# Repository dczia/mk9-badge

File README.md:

```
___  ____     _____  ______           _            
|  \/  | |   |  _  | | ___ \         | |           
| .  . | | __| |_| | | |_/ / __ _  __| | __ _  ___ 
| |\/| | |/ /\____ | | ___ \/ _` |/ _` |/ _` |/ _ \
| |  | |   < .___/ / | |_/ / (_| | (_| | (_| |  __/
\_|  |_/_|\_\\____/  \____/ \__,_|\__,_|\__, |\___|
                                         __/ |     
                                        |___/      
-------------------------------------------------
D C Z I A  ----------  2 0 2 6
```

DCZia Presents: The MK9 Badge

It blinks. It types. You can wear it around your neck and then set it on your desk and actually use it\*.

\* _Desk productivity not guaranteed. DCZia assumes no responsibility for keys accidentally sent during badge parties. Consult your keyboard layer documentation before operating heavy machinery._

---

## About

The **MK9** is a fully functional **3×3 mechanical macropad badge**. Nine real mechanical switches, per-key RGB lighting, ambient underglow, an accelerometer that actually does something interesting, SAO support, and CircuitPython firmware out of the box — all in a package sized to hang around your neck at DEF CON and survive the week.

---

## Specs

**Keys**
- 9× mechanical switches in a 3×3 grid — standard MX footprint, swap keycaps as you please
- Ships with translucent blue keycaps
- Full N-key rollover USB HID keyboard when plugged into a computer

**Lighting**
- 9× WS2812B per-key RGB LEDs — one under each switch
- 6× SK6812 side-firing LEDs — edge-mounted for ambient underglow out the sides

**Brains & Sensors**
- RP2040 microcontroller
- 3-axis accelerometer — tilt-reactive lighting, shake to change patterns
- 2× SAO connectors (standard 6-pin, I2C + 2 GPIO each) — expand with the badge add-on ecosystem

**Power & I/O**
- USB-C — power and data
- 3× AAA battery pack — run it untethered
- Power switch for battery mode
- Reset button + BOOTSEL button for easy firmware flashing

**Firmware**
- Ships with CircuitPython firmware
- QMK-compatible hardware — reflash and run it as a full QMK macropad

---

## What It Does Out of the Box

On boot: a rainbow diagonal wipe sweeps across the keys and backlights. Any keypress skips it.

Once running:
- Background light patterns cycle across all 15 LEDs — rainbow wave, breathing pulse, or sparkle
- Pressing a key sends a colour ripple expanding outward from that key through all the LEDs
- Tilt the badge to shift the colour palette; shake it to switch patterns
- Plug into a computer and it shows up as a numpad (7–9 / 4–6 / 1–3 layout)

---

## Repository

```
mk9-badge/
├── buildguide.md — badge assembly, flashing, and troubleshooting
├── hardware/   — KiCad design files, BOM, fabrication outputs
└── software/   — MicroPython firmware
```

- [Build Guide →](buildguide.md) — assembly, battery installation, flashing, and troubleshooting
- [Hardware →](hardware/README.md) — schematics, PCB layout, drill files, BOM
- [Software →](software/README.md) — firmware architecture, pinout, library requirements, flashing instructions

**Fabrication outputs**:
- [PCB layer plot](hardware/output/mk9-badge.pdf)
- [PTH drill map](hardware/output/mk9-badge-PTH-drl_map.pdf)
- [NPTH drill map](hardware/output/mk9-badge-NPTH-drl_map.pdf)

---

## Programming / Updating

The badge runs [CircuitPython](https://circuitpython.org). To update the firmware:

1. Hold **BOOTSEL** while plugging the badge into your computer — it mounts as `RPI-RP2`.
2. Drag the CircuitPython `.uf2` onto the drive. It reboots as `CIRCUITPY`.
3. Copy the `lib/` folder contents to `CIRCUITPY/lib/` (see [software/README.md](software/README.md) for the library list).
4. Copy all `.py` files from `software/` to the root of `CIRCUITPY`.

The badge restarts automatically. If it gets into a weird state, delete everything on `CIRCUITPY` and start fresh — it won't brick.

Want to run QMK instead? The hardware is fully compatible; QMK setup instructions will be posted separately.

**Recommended IDEs:** Visual Studio Code with the [CircuitPython extension](https://marketplace.visualstudio.com/items?itemName=ms-python.python), or [Thonny](https://thonny.org). A Commodore 64 with a serial adapter also works but is left as an exercise for the reader.

---

## Open Source

DCZia is committed to open source hardware and software. All design files and firmware are publicly available.

- **Live CAD (OnShape):** [View the design](https://cad.onshape.com/documents/36884624fbe35c16a5af61a7/w/233227193d278274727a44c3/e/ea987b4b53c4648fa3dc84b6)

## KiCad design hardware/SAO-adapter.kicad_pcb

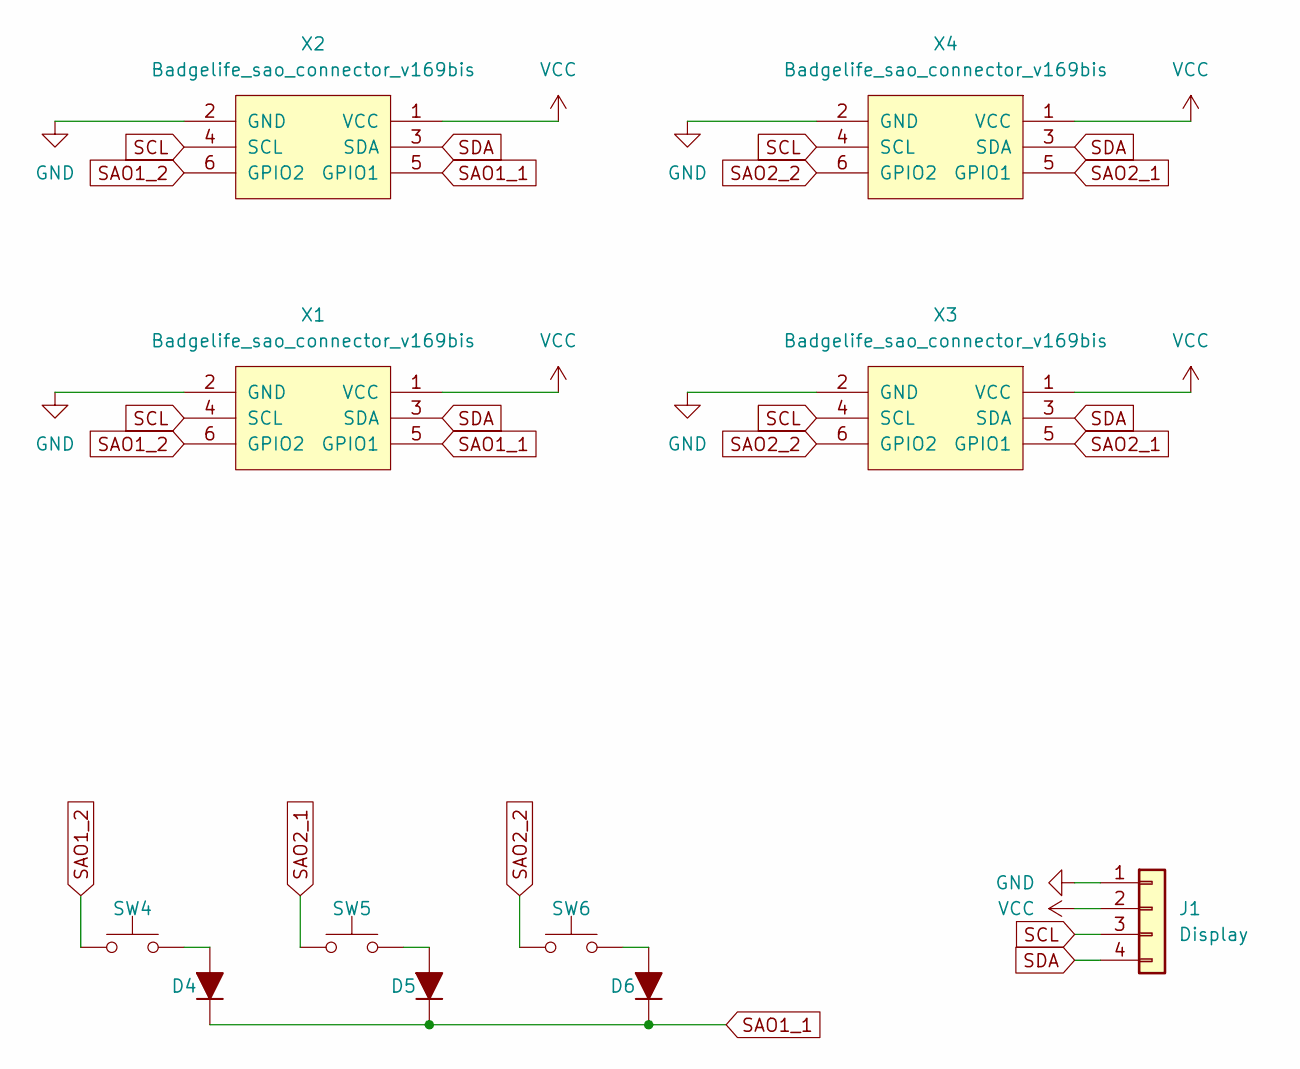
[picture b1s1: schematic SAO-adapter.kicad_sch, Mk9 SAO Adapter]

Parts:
D4, D5, D6: D_Schottky; D_SOD-123F
J1: Display; PinHeader_1x04_P2.54mm_Vertical
SW4, SW5, SW6: SW_Push; MX-Alps-Choc-1U-NoFrontMask
X1, X3: Badgelife_sao_connector_v169bis; Badgelife-Shitty-v1.69bis-No-Silk
X2, X4: Badgelife_sao_connector_v169bis; Badgelife-Shitty-v1.69bis-Minimal-Front

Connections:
GND: J1.1, X1.2 (GND), X2.2 (GND), X3.2 (GND), X4.2 (GND)
unnamed: D4.2 (A), SW4.2
unnamed: D5.2 (A), SW5.2
unnamed: D6.2 (A), SW6.2
SAO1_1: D4.1 (K), D5.1 (K), D6.1 (K), X1.5 (GPIO1), X2.5 (GPIO1)
SAO1_2: SW4.1, X1.6 (GPIO2), X2.6 (GPIO2)
SAO2_1: SW5.1, X3.5 (GPIO1), X4.5 (GPIO1)
SAO2_2: SW6.1, X3.6 (GPIO2), X4.6 (GPIO2)
SCL: J1.3, X1.4 (SCL), X2.4 (SCL), X3.4 (SCL), X4.4 (SCL)
SDA: J1.4, X1.3 (SDA), X2.3 (SDA), X3.3 (SDA), X4.3 (SDA)
VCC: J1.2, X1.1 (VCC), X2.1 (VCC), X3.1 (VCC), X4.1 (VCC)

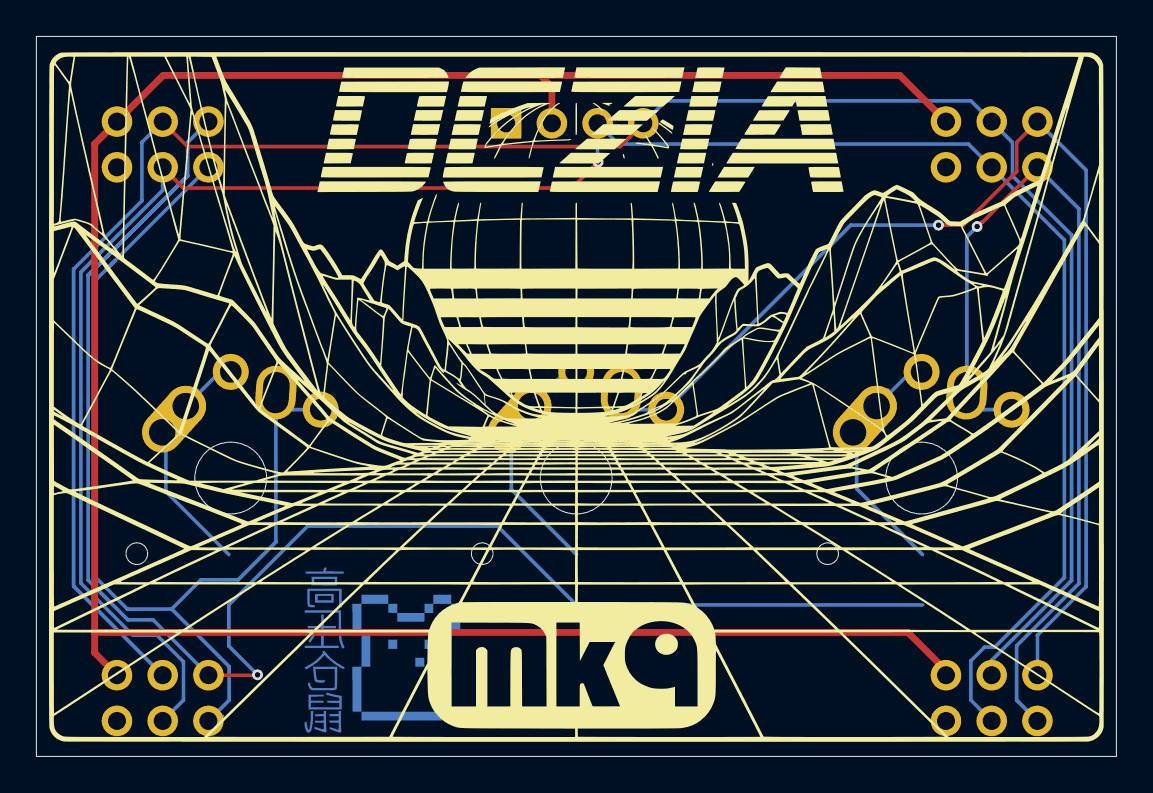
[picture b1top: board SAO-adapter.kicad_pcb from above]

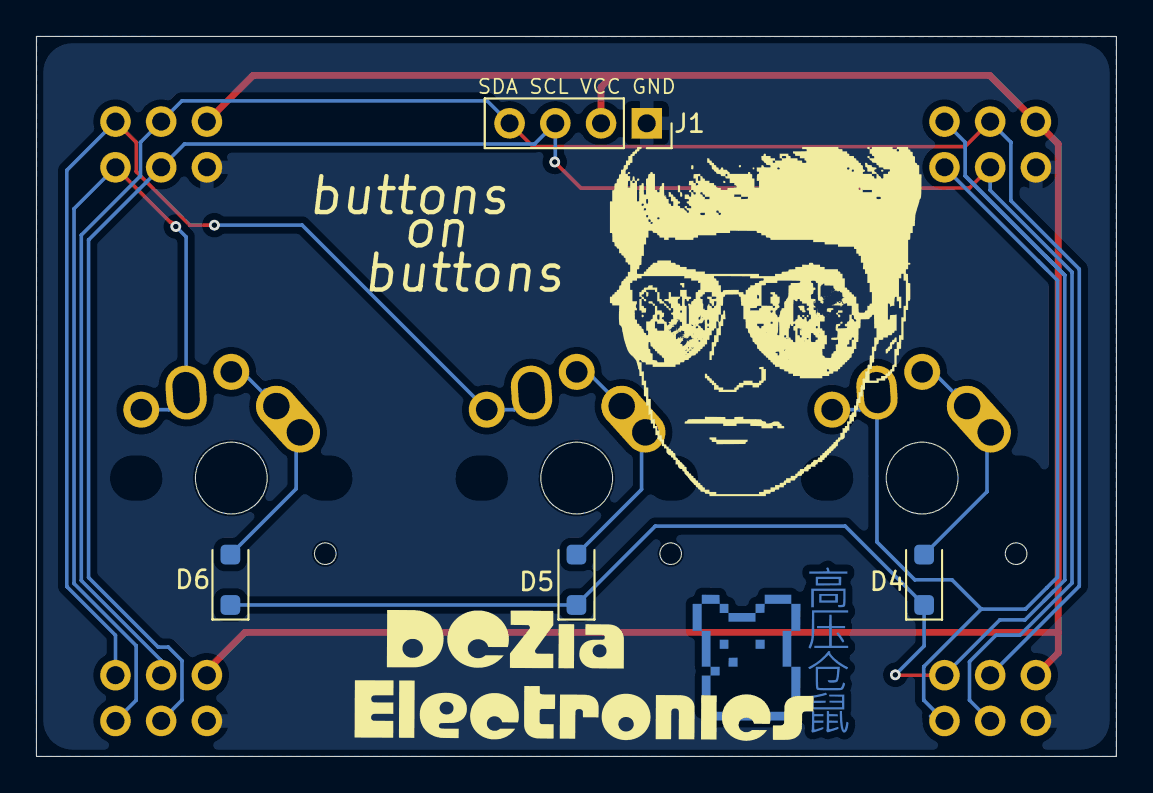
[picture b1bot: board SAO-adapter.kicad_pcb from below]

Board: 2 copper layers, 60.0 x 40.0 mm, 11 parts (3 on the bottom side), 11 nets.

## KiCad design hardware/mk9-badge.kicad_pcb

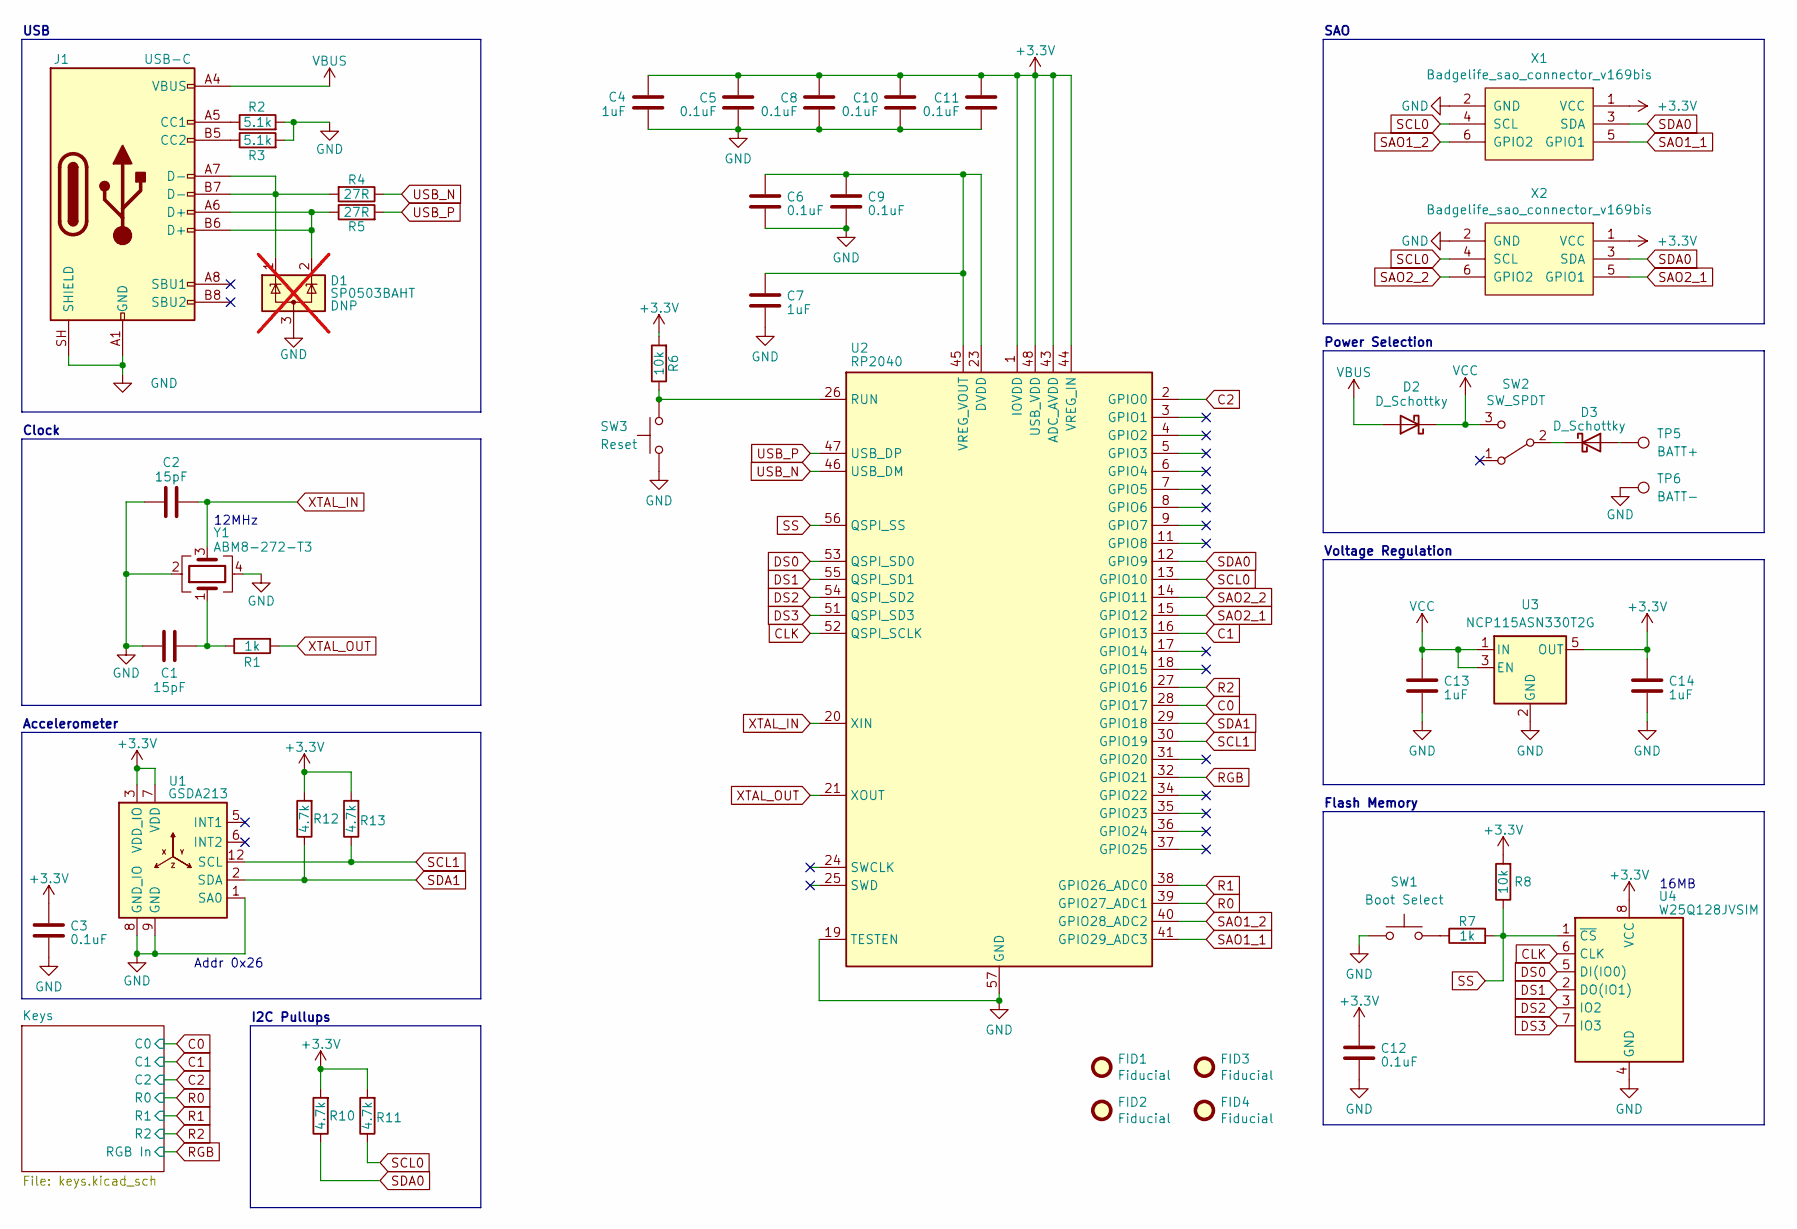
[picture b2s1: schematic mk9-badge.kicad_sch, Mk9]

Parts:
C1, C2: 15pF; C_0603_1608Metric
C3, C5, C6, C8, C9, C10, C11, C12: 0.1uF; C_0603_1608Metric
C4, C7, C13, C14: 1uF; C_0603_1608Metric
D1: SP0503BAHT; SOT-23-3; not fitted
D2, D3: D_Schottky; D_SOD-123F
FID1, FID2, FID3, FID4: Fiducial; Fiducial_1mm_Mask2mm
J1: USB-C; USB_C_Receptacle_HCTL_HC-TYPE-C-16P-01A
R1, R7: 1k; R_0603_1608Metric
R2, R3: 5.1k; R_0603_1608Metric
R4, R5: 27R; R_0603_1608Metric
R6, R8: 10k; R_0603_1608Metric
R10, R11, R12, R13: 4.7k; R_0603_1608Metric
SW1: Boot Select; SW_SPST_EVQP7C
SW2: SW_SPDT; SW_SPDT_CK-JS102011SAQN
SW3: Reset; SW_SPST_EVQP7C
TP5: BATT+; TestPoint_Pad_2.5x2.5mm
TP6: BATT-; TestPoint_Pad_2.5x2.5mm
U1: GSDA213; Kionix_LGA-12_2x2mm_P0.5mm_LayoutBorder2x4y
U2: RP2040; QFN-56-1EP_7x7mm_P0.4mm_EP3.2x3.2mm
U3: NCP115ASN330T2G; SOT-23-5
U4: W25Q128JVSIM; SOIC-8_5.3x5.3mm_P1.27mm
X1, X2: Badgelife_sao_connector_v169bis; Badgelife-Shitty-v1.69bis
Y1: ABM8-272-T3; Crystal_SMD_Abracon_ABM8G-4Pin_3.2x2.5mm

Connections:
C0: U2.28 (GPIO17); also elsewhere on the board
C1: U2.16 (GPIO13); also elsewhere on the board
C2: U2.2 (GPIO0); also elsewhere on the board
CLK: U2.52 (QSPI_SCLK), U4.6 (CLK)
DS0: U2.53 (QSPI_SD0), U4.5 (DI(IO0))
DS1: U2.55 (QSPI_SD1), U4.2 (DO(IO1))
DS2: U2.54 (QSPI_SD2), U4.3 (IO2)
DS3: U2.51 (QSPI_SD3), U4.7 (IO3)
GND: C1.1, C2.1, C3.1, C4.1, C5.1, C6.1, C7.1, C8.1, C9.1, C10.1, C11.1, C12.1, C13.1, C14.1, D1.3 (A), J1.A1 (GND), J1.A12 (GND), J1.B1 (GND), J1.B12 (GND), J1.SH (SHIELD), R2.2, R3.2, SW1.1, SW3.1, TP6.1 (1_1), U1.1 (SA0), U1.8 (GND_IO), U1.9 (GND), U2.19 (TESTEN), U2.57 (GND), U3.2 (GND), U4.4 (GND), X1.2 (GND), X2.2 (GND), Y1.2, Y1.4; also elsewhere on the board
unnamed: C1.2, R1.1, Y1.1
unnamed: D1.1 (K), J1.A7 (D-), J1.B7 (D-), R4.2
unnamed: D1.2 (K), J1.A6 (D+), J1.B6 (D+), R5.1
unnamed: D3.2 (A), TP5.1 (1_1)
unnamed: D3.1 (K), SW2.2 (B)
unnamed: J1.A5 (CC1), R2.1
unnamed: J1.B5 (CC2), R3.1
unnamed: R7.1, SW1.2
unnamed: R6.1, SW3.2, U2.26 (RUN)
unnamed: C6.2, C7.2, C9.2, U2.23 (DVDD), U2.45 (VREG_VOUT), U2.50 (DVDD)
R0: U2.39 (GPIO27_ADC1); also elsewhere on the board
R1: U2.38 (GPIO26_ADC0); also elsewhere on the board
R2: U2.27 (GPIO16); also elsewhere on the board
RGB: U2.32 (GPIO21); also elsewhere on the board
SAO1_1: U2.41 (GPIO29_ADC3), X1.5 (GPIO1)
SAO1_2: U2.40 (GPIO28_ADC2), X1.6 (GPIO2)
SAO2_1: U2.15 (GPIO12), X2.5 (GPIO1)
SAO2_2: U2.14 (GPIO11), X2.6 (GPIO2)
SCL0: R11.1, U2.13 (GPIO10), X1.4 (SCL), X2.4 (SCL)
SCL1: R13.1, U1.12 (SCL), U2.30 (GPIO19)
SDA0: R10.1, U2.12 (GPIO9), X1.3 (SDA), X2.3 (SDA)
SDA1: R12.1, U1.2 (SDA), U2.29 (GPIO18)
SS: R7.2, R8.1, U2.56 (QSPI_SS), U4.1 (~CS)
USB_N: R4.1, U2.46 (USB_DM)
USB_P: R5.2, U2.47 (USB_DP)
VBUS: D2.2 (A), J1.A4 (VBUS), J1.A9 (VBUS), J1.B4 (VBUS), J1.B9 (VBUS)
XTAL_IN: C2.2, U2.20 (XIN), Y1.3
XTAL_OUT: R1.2, U2.21 (XOUT)

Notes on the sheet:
Addr 0x26
Clock
12MHz
USB
Power Selection
Voltage Regulation
Flash Memory
I2C Pullups
Accelerometer
16MB
SAO

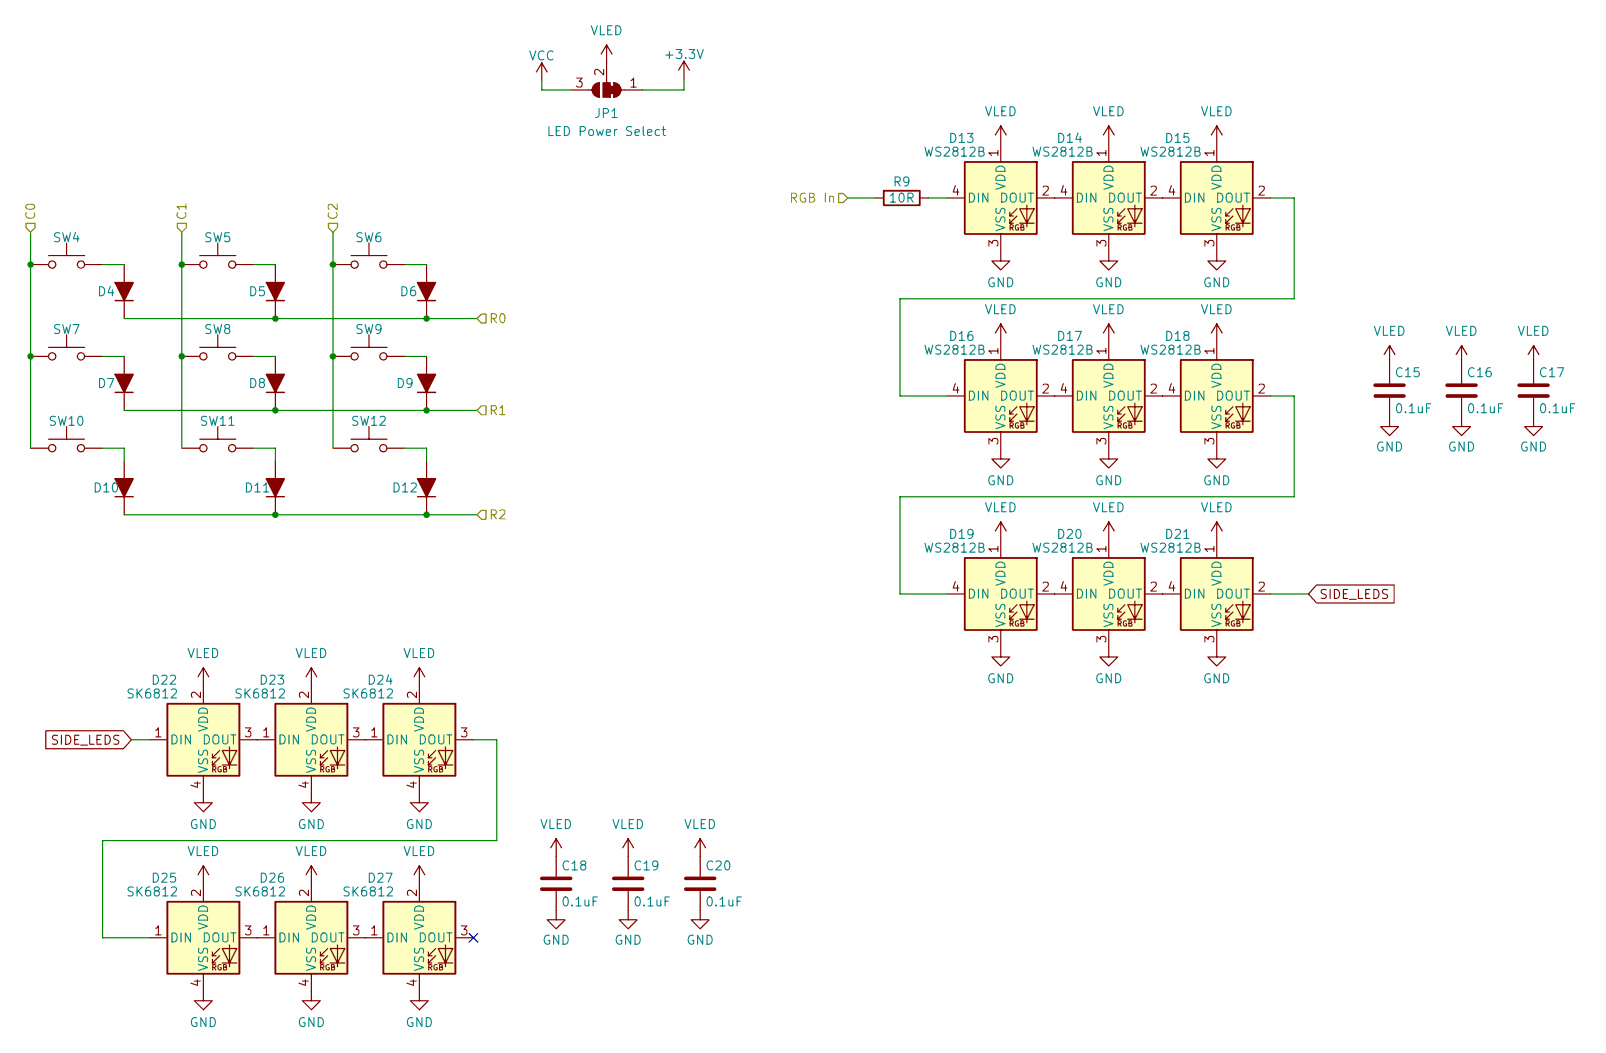
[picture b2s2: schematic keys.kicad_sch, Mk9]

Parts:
C15, C16, C17, C18, C19, C20: 0.1uF; C_0603_1608Metric
D4, D5, D6, D7, D8, D9, D10, D11, D12: D_Schottky; D_SOD-123F
D13, D14, D15, D16, D17, D18, D19, D20, D21: WS2812B; LED_WS2812B_PLCC4_5.0x5.0mm_P3.2mm_Update
D22, D23, D24, D25, D26, D27: SK6812; LED_SK6812_4020
JP1: LED Power Select; SolderJumper-3_P1.3mm_Bridged2Bar12_RoundedPad1.0x1.5mm
R9: 10R; R_0603_1608Metric
SW4, SW5, SW6, SW7, SW8, SW9, SW10, SW11, SW12: SW_Push; CHERRY_SMDLED_100H

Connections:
C0: SW4.1, SW7.1, SW10.1; also elsewhere on the board
C1: SW5.1, SW8.1, SW11.1; also elsewhere on the board
C2: SW6.1, SW9.1, SW12.1; also elsewhere on the board
GND: C15.2, C16.2, C17.2, C18.2, C19.2, C20.2, D13.3 (VSS), D14.3 (VSS), D15.3 (VSS), D16.3 (VSS), D17.3 (VSS), D18.3 (VSS), D19.3 (VSS), D20.3 (VSS), D21.3 (VSS), D22.4 (VSS), D23.4 (VSS), D24.4 (VSS), D25.4 (VSS), D26.4 (VSS), D27.4 (VSS); also elsewhere on the board
unnamed: D4.2 (A), SW4.2
unnamed: D5.2 (A), SW5.2
unnamed: D6.2 (A), SW6.2
unnamed: D7.2 (A), SW7.2
unnamed: D8.2 (A), SW8.2
unnamed: D9.2 (A), SW9.2
unnamed: D10.2 (A), SW10.2
unnamed: D11.2 (A), SW11.2
unnamed: D12.2 (A), SW12.2
unnamed: D13.4 (DIN), R9.1
unnamed: D13.2 (DOUT), D14.4 (DIN)
unnamed: D14.2 (DOUT), D15.4 (DIN)
unnamed: D15.2 (DOUT), D16.4 (DIN)
unnamed: D16.2 (DOUT), D17.4 (DIN)
unnamed: D17.2 (DOUT), D18.4 (DIN)
unnamed: D18.2 (DOUT), D19.4 (DIN)
unnamed: D19.2 (DOUT), D20.4 (DIN)
unnamed: D20.2 (DOUT), D21.4 (DIN)
unnamed: D22.3 (DOUT), D23.1 (DIN)
unnamed: D23.3 (DOUT), D24.1 (DIN)
unnamed: D24.3 (DOUT), D25.1 (DIN)
unnamed: D25.3 (DOUT), D26.1 (DIN)
unnamed: D26.3 (DOUT), D27.1 (DIN)
R0: D4.1 (K), D5.1 (K), D6.1 (K); also elsewhere on the board
R1: D7.1 (K), D8.1 (K), D9.1 (K); also elsewhere on the board
R2: D10.1 (K), D11.1 (K), D12.1 (K); also elsewhere on the board
RGB: R9.2; also elsewhere on the board
SIDE_LEDS: D21.2 (DOUT), D22.1 (DIN)
VLED: C15.1, C16.1, C17.1, C18.1, C19.1, C20.1, D13.1 (VDD), D14.1 (VDD), D15.1 (VDD), D16.1 (VDD), D17.1 (VDD), D18.1 (VDD), D19.1 (VDD), D20.1 (VDD), D21.1 (VDD), D22.2 (VDD), D23.2 (VDD), D24.2 (VDD), D25.2 (VDD), D26.2 (VDD), D27.2 (VDD), JP1.2 (C)

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
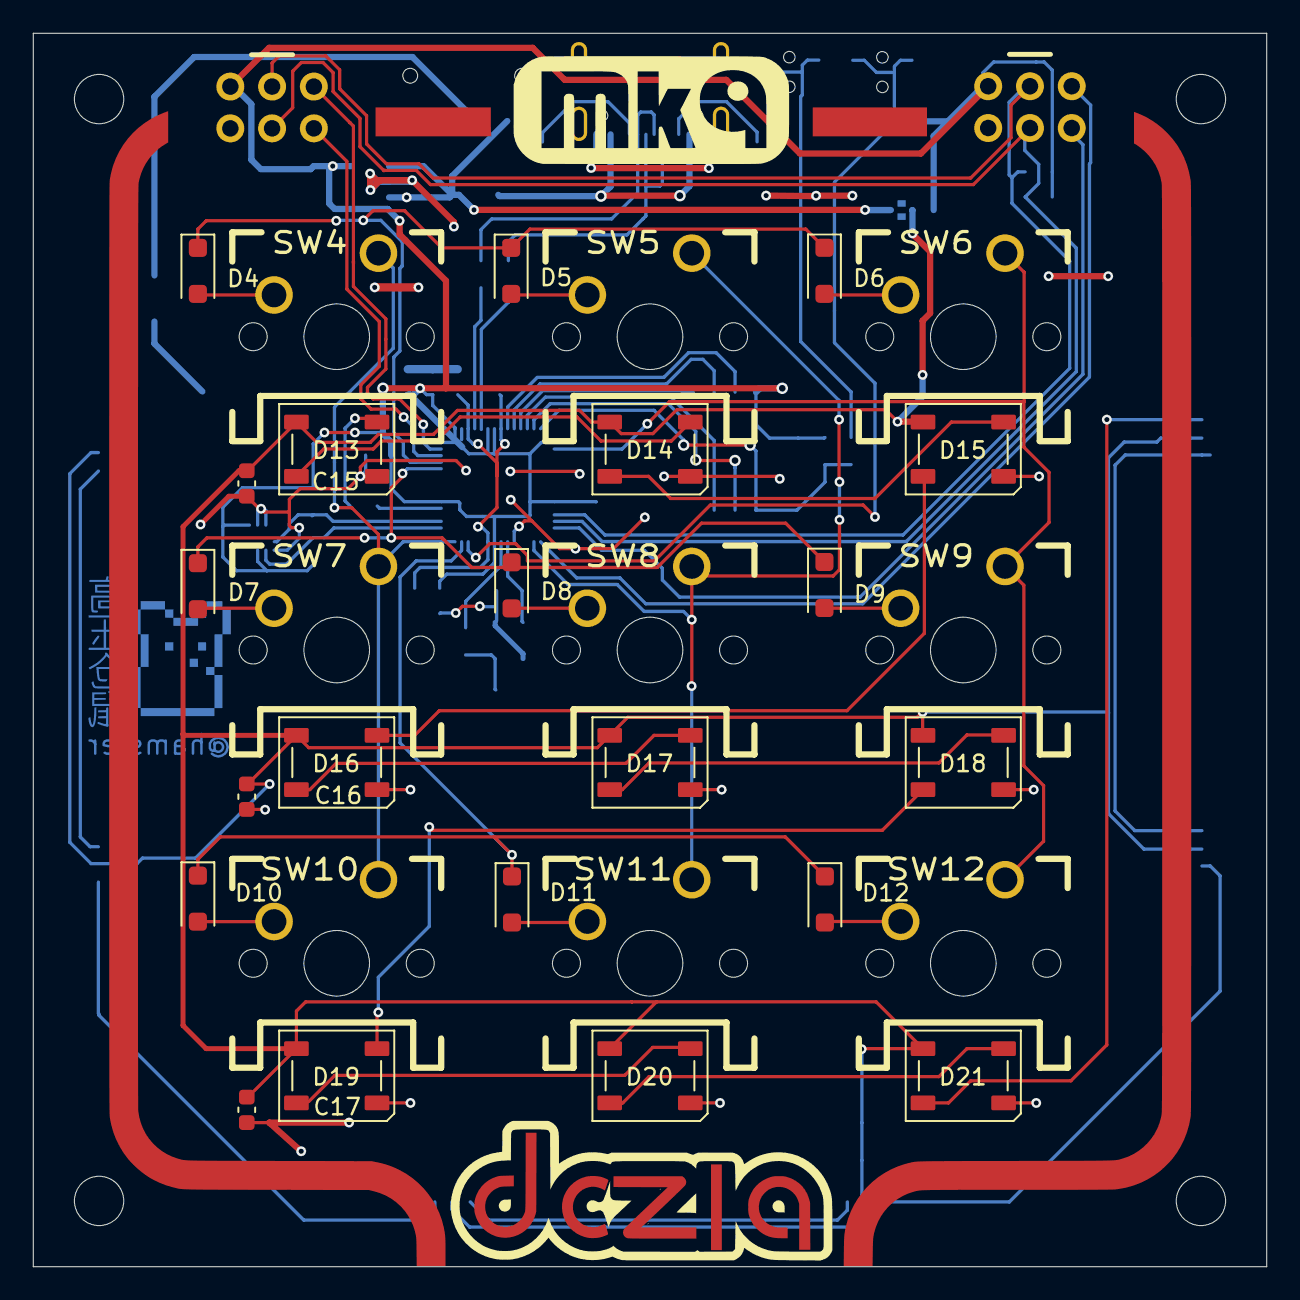
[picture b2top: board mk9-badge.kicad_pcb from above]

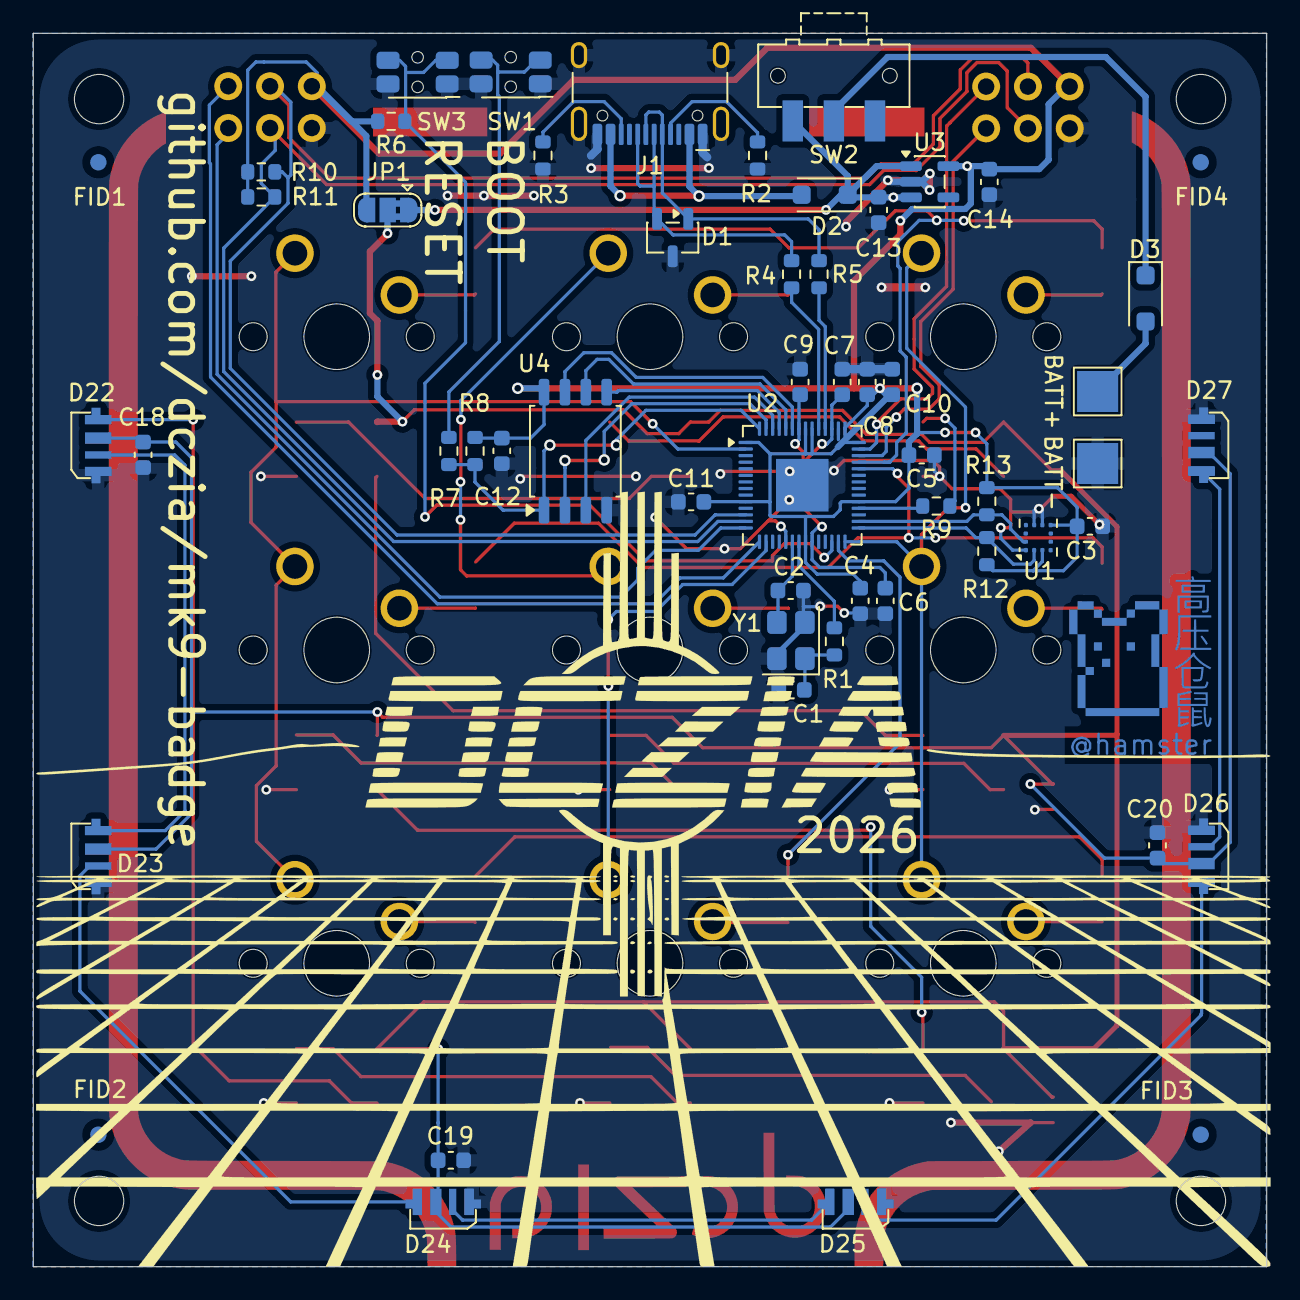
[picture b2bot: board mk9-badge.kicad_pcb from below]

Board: 2 copper layers, 75.0 x 75.0 mm, 87 parts (55 on the bottom side), 64 nets.

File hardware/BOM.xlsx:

Reference | Feeder | Value | Footprint | Part Number | Distributor | Distributor Part | Datasheet | Qty | Cost Each | Qty Ordered | QOH | Notes
C3,C5,C6,C8-C12,C15-C20 | 6 | 0.1uF | 0603 |  |  |  | ~ | 14 | 4.0000000000000001E-3 | 0 | 2500
C4,C7,C13,C14 | 7 | 1uF | 0603 |  |  |  | ~ | 4 | 4.0000000000000001E-3 | 0 | 3500
C1,C2 | 8 | 15pF | 0603 |  |  |  | ~ | 2 | 4.0000000000000001E-3 | 0 | 3500
D2-12 | 9 | D_Schottky | SOD-123 |  | Digikey | 3757-SS0540_R1_00001DKR-ND | https://www.panjit.com.tw/upload/datasheet/SS0520_SERIES.pdf | 2 | 0.11 | 0 | 2500
D13-21 | 23 | WS2812B | LED_SMD:LED_WS2812B_PLCC4_5.0x5.0mm_P3.2mm |  | Aliexpress | https://www.aliexpress.us/item/2251832628463811.html?spm=a2g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 | https://cdn-shop.adafruit.com/datasheets/WS2812B.pdf | 9 | 7.0000000000000007E-2 | 0 | 2000
D22-27 | 22 | SK6812 |  |  | Aliexpress |  |  | 6 | 0.1 | 1000 | 0
D1 |  | TVS |  | SP0502BAHTG | Mouser | 576-SP0502BAHTG | https://www.littelfuse.com/assetdocs/tvs-diode-array-spasp05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 | 0 | 0.38300000000000001 |  |  | Optional stuffing
J1 |  | USB-C | Connector_USB:USB_C_Receptacle_HCTL_HC-TYPE-C-16P-01A |  | Aliexpress | https://www.aliexpress.us/item/3256805324706422.html?spm=a2g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 | https://www.lcsc.com/datasheet/lcsc_datasheet_2211161000_HCT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 | 1 | 0.19 | 150 | 100
R1,R7 | manual | 1k | 0603 |  |  |  | ~ | 2 | 1E-3 | 0 | 4500
R6,R8 | 1 | 10k | 0603 |  |  |  | ~ | 2 | 1E-3 | 0 | 4500
R2,R3 | 5 | 5.1k | 0603 |  |  |  | ~ | 2 | 1E-3 | 0 | 4500
R4,R5 | 2 | 27R | 0603 |  |  |  | ~ | 2 | 1E-3 | 0 | 4500
R9 | manual | 10R | 0603 |  |  |  | ~ | 1 | 1E-3 | 0 | 4500
R10,R11 | 3 | 4.7k | 0603 |  |  |  |  | 2 | 1E-3 | 5000 | 0
S1,S3 | after | SPST Push w/boss | Button_Switch_SMD:SW_SPST_EVQP7C | EVQ-P7C01P | Digikey | P16765CT-ND | https://api.pim.na.industrial.panasonic.com/file_stream/main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 | 2 | 0.20204 | 300 | 0
S2 | after | SW_SPDT | lib_fp:SW_SPDT_CK-JS102011SAQN | JS102011SAQN | Digikey | 401-1999-1-ND | https://ckswitches.com/media/1422/js.pdf | 1 | 0.60319999999999996 | 150 | 0
S4-12 |  | CherryMX Blue |  |  | Aliexpress |  |  | 9 | 0.1 | 1000 | 0
U3 | 10 | NCP115ASN330T2G | Package_TO_SOT_SMD:SOT-23-5 | NCP115ASN330T2G | Digikey | NCP115ASN330T2G | https://www.onsemi.com/pdf/datasheet/ncp115-d.pdf | 1 | 6.7699999999999996E-2 | 0 | 2500
U2 | 30 | RP2040 | Package_DFN_QFN:QFN-56-1EP_7x7mm_P0.4mm_EP3.2x3.2mm | SC0914(7) | Mouser | 358-SC09147 | https://datasheets.raspberrypi.com/rp2040/rp2040-datasheet.pdf | 1 | 0.8 | 0 | 1000
U4 | after | W25Q128JVSIM |  |  | Digikey | W25Q128JVSIM-ND | https://www.winbond.com/resource-files/W25Q128JV%20RevI%2008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 | 1 | 2.5155599999999998 | 133 | 0
U1 | manual | GSDA213 | Kionix_LGA-12_2x2mm_P0.5mm_LayoutBorder2x4y | GSDA213 | Digikey | 4786-GSDA213TR-ND | https://goodarksemi.com/docs/datasheets/mems/GSDA213_SDS.pdf | 1 | 0.65949999999999998 | 150 | 0
X1,X2 |  | Badgelife_sao_connector_v169bis | lib_fp:Badgelife-Shitty-v1.69bis | VIRTUAL |  |  |  | 2
Y1 | manual | Crystal | Crystal:Crystal_SMD_3225-4Pin_3.2x2.5mm | ABM8-272-T3 | Digikey | 535-ABM8-272-T3DKR-ND | https://abracon.com/datasheets/ABM8-272-T3.pdf | 1 | 0.40849999999999997 | 150 | 0
 |  | Key caps |  |  |  |  |  | 9 | 0.19 | 1500
` |  | Battery boxes |  |  |  |  |  | 1 |  | 125
 |  | PCB |  |  |  |  |  | 1 |  | 200
 |  | Batteries |  |  | Amazon |  |  | 3 | 0.15 | 300
 |  | Badge Run, units | 120
